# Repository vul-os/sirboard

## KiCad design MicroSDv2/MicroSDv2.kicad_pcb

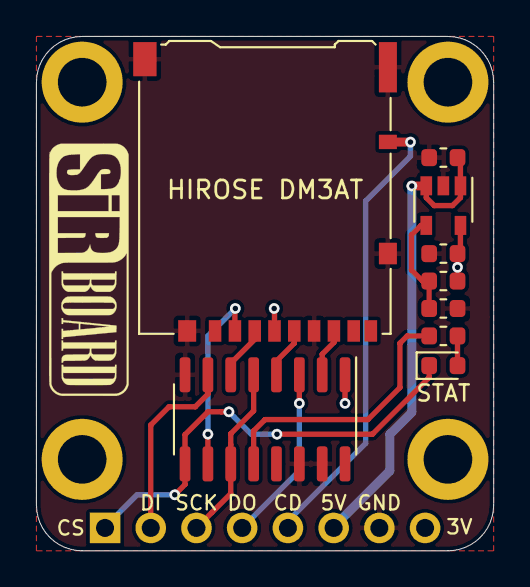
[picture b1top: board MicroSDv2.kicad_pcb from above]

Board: 2 copper layers, 25.4 x 28.6 mm, 14 parts (1 on the bottom side), 15 nets.

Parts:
C1, C2: 1uF; C_0603_1608Metric
H1, H2, H3, H4: MountingHole; MountingHole_2.7mm_M2.5_ISO14580_Pad
HIROSE DM3AT: Micro_SD_Card_Det; microSD_HC_Hirose_DM3AT-SF-PEJM5
J1: Conn_01x08; PinHeader_1x08_P2.54mm_Vertical
R1: 31K6; R_0603_1608Metric
R3: 10K; R_0603_1608Metric
R6: 1K; R_0603_1608Metric
STAT: LED; LED_0603_1608Metric
U1: AP7365; SOT-23-5
U2: 4050; SOIC-16_3.9x9.9mm_P1.27mm

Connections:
/CLK_SD: HIROSE DM3AT.5, U2.4
/CS_SD: HIROSE DM3AT.2, U2.10
/DI_SD: HIROSE DM3AT.3, U2.6
/DO_SD: HIROSE DM3AT.7, U2.2
ADJ: R1.2, R3.1, U1.4
CS: J1.1, STAT.1, U2.9
DETA: HIROSE DM3AT.10, J1.5
DI: J1.2, U2.7
DO: J1.4, U2.3
GND: C1.2, C2.2, HIROSE DM3AT.6, HIROSE DM3AT.11, J1.7, R3.2, U1.2, U2.8, U2.14, U2.15
unnamed: R6.2, STAT.2
unnamed: R6.1, U2.12
SCK: J1.3, U2.5, U2.11
VIN: C1.1, J1.6, U1.1, U1.3
VOUT: C2.1, HIROSE DM3AT.4, J1.8, R1.1, U1.5, U2.1

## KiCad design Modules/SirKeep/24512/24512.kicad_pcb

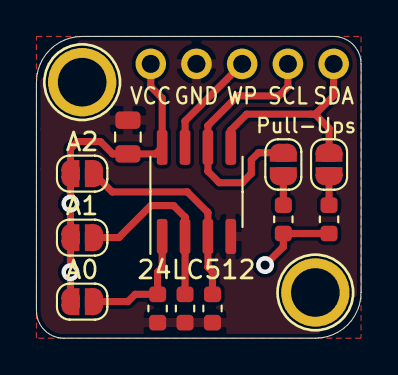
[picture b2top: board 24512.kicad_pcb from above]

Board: 2 copper layers, 18.0 x 16.8 mm, 15 parts (0 on the bottom side), 10 nets.

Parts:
24LC512: 24LC1025; SOIC-8_3.9x4.9mm_P1.27mm
A0, A1, A2: SolderJumper_2_Open; SolderJumper-2_P1.3mm_Open_RoundedPad1.0x1.5mm
C1: 1uF; C_0805_2012Metric
H1, H2: MountingHole; MountingHole_M2.5_SirBoard
J1: Conn_01x05; PinHeader_1x05_P2.54mm_Vertical
R1, R2: 4K7; R_0603_1608Metric
R3, R4, R5: 10K; R_0603_1608Metric
SCL: SolderJumper_2_Open; SolderJumper-2_P1.3mm_Open_RoundedPad1.0x1.5mm
SDA: SolderJumper_2_Open; SolderJumper-2_P1.3mm_Open_RoundedPad1.0x1.5mm

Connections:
/A0: 24LC512.1, A0.1, R3.1
/A1: 24LC512.2, A1.1, R4.1
/A2: 24LC512.3, A2.1, R5.1
GND: 24LC512.4, C1.2, J1.2, R3.2, R4.2, R5.2
unnamed: R1.1, SCL.2
unnamed: R2.1, SDA.2
SCL: 24LC512.6, J1.4, SCL.1
SDA: 24LC512.5, J1.5, SDA.1
VCC: 24LC512.8, A0.2, A1.2, A2.2, C1.1, J1.1, R1.2, R2.2
WP: 24LC512.7, J1.3

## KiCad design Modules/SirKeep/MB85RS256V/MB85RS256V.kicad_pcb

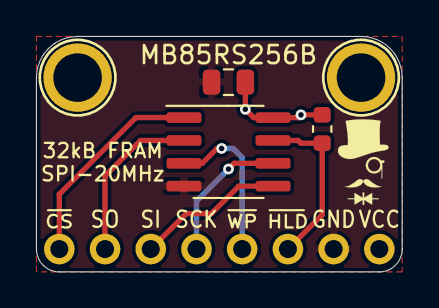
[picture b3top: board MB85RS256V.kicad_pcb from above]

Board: 2 copper layers, 20.3 x 13.1 mm, 6 parts (1 on the bottom side), 8 nets.

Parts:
C1: 10uF; C_0805_2012Metric
H1, H2: MountingHole; MountingHole_M2.5_SirBoard
J1: Conn_01x08; PinHeader_1x08_P2.54mm_Vertical
MB85RS256B: MB85RS64; SOIC-8_3.9x4.9mm_P1.27mm
R3: 10K; R_0603_1608Metric

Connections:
CS: J1.1, MB85RS256B.1
GND: C1.2, J1.7, MB85RS256B.4
HOLD: J1.6, MB85RS256B.7, R3.2
SCK: J1.4, MB85RS256B.6
SI: J1.3, MB85RS256B.5
SO: J1.2, MB85RS256B.2
VCC: C1.1, J1.8, MB85RS256B.8, R3.1
WP: J1.5, MB85RS256B.3

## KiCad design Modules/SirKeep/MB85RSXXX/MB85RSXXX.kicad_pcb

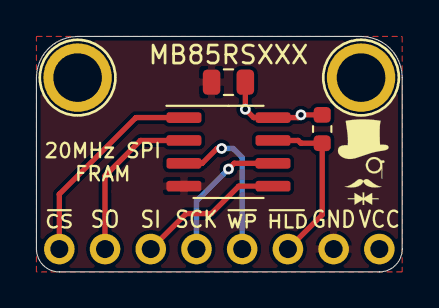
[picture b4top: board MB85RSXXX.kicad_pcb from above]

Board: 2 copper layers, 20.3 x 13.1 mm, 6 parts (1 on the bottom side), 8 nets.

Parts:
C1: 10uF; C_0805_2012Metric
H1, H2: MountingHole; MountingHole_M2.5_SirBoard
J1: Conn_01x08; PinHeader_1x08_P2.54mm_Vertical
MB85RSXXX: MB85RS64; SOIC-8_3.9x4.9mm_P1.27mm
R3: 10K; R_0603_1608Metric

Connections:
CS: J1.1, MB85RSXXX.1
GND: C1.2, J1.7, MB85RSXXX.4
HOLD: J1.6, MB85RSXXX.7, R3.2
SCK: J1.4, MB85RSXXX.6
SI: J1.3, MB85RSXXX.5
SO: J1.2, MB85RSXXX.2
VCC: C1.1, J1.8, MB85RSXXX.8, R3.1
WP: J1.5, MB85RSXXX.3

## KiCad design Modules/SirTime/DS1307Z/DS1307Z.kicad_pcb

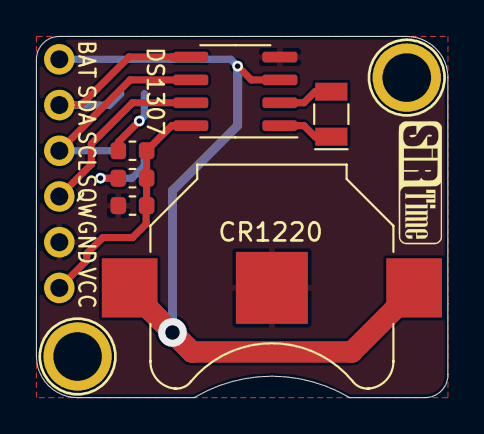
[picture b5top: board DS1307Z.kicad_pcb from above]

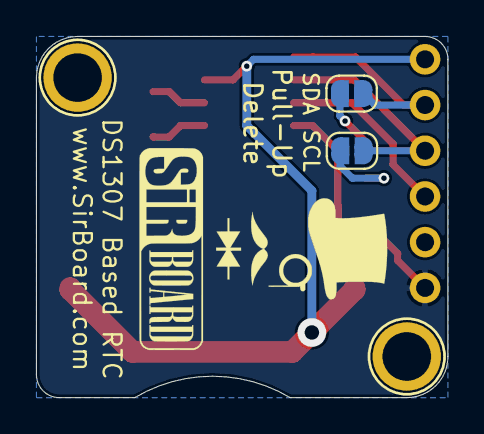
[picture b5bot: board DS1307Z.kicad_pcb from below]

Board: 2 copper layers, 22.9 x 20.1 mm, 9 parts (3 on the bottom side), 10 nets.

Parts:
C1: 1uF; C_0603_1608Metric
CR1220: Battery_Cell; BatteryHolder_Keystone_3000_1x12mm
DS1307: DS1307Z+; SOIC-8_3.9x4.9mm_P1.27mm
J1: Conn_01x06; PinHeader_1x06_P2.54mm_Vertical
R1, R2: 4K7; R_0603_1608Metric
SCL: SolderJumper_2_Open; SolderJumper-2_P1.3mm_Open_RoundedPad1.0x1.5mm
SDA: SolderJumper_2_Open; SolderJumper-2_P1.3mm_Open_RoundedPad1.0x1.5mm
Y1: Crystal; Crystal_SMD_EuroQuartz_EQ161-2Pin_3.2x1.5mm

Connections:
GND: C1.2, CR1220.2, DS1307.4, J1.5
unnamed: R1.1, SDA.2
unnamed: R2.1, SCL.2
unnamed: DS1307.1, Y1.1
unnamed: DS1307.2, Y1.2
SCL: DS1307.6, J1.3, SCL.1
SDA: DS1307.5, J1.2, SDA.1
SQW: DS1307.7, J1.4
VBAT: CR1220.1, DS1307.3, J1.1
VCC: C1.1, DS1307.8, J1.6, R1.2, R2.2
